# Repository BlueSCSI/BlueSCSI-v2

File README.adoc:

# BlueSCSI
:toc: macro

BlueSCSI is hardware that reproduces SCSI devices (hard disks, optical, etc) powered by the Raspberry Pi RP2040/RP2350.

This repository contains code for both BlueSCSI v2 and BlueSCSI Ultra/Ultra Wide.

image::docs/buynow.png[Buy Now,link=https://scsi.blue,width=150]
image::docs/discordbanner.png[Join our Discord,link=https://discord.gg/GKcvtgU7P9,width=150]

Join us in #bluescsi on https://discord.gg/GKcvtgU7P9[Discord] or open an issue on this repo.

## Hardware

Hardware schematics, designs, and production files can be found under the `hardware` folder.

Hardware version numbers are based on when the design was updated plus a sub-revision letter, such as "2022_11b" and "2022_12a".

You can find an errta of all the current and former versions in the wiki https://github.com/BlueSCSI/BlueSCSI-v2/wiki/Hardware

## Notes

### Making Gerbers for JLCPCB

https://support.jlcpcb.com/article/44-how-to-export-kicad-pcb-to-gerber-files

## Licenses

### Firmware

The BlueSCSI V2 firmware is a fork of ZuluSCSI, which also includes SCSI2SD V6 source code:

* https://github.com/ZuluSCSI/ZuluSCSI-firmware[ZuluSCSI]
* http://git.codesrc.com/index.cgi?p=SCSI2SD-V6.git;a=summary[SCSI2SD V6]
* https://github.com/erichelgeson/BlueSCSI[BlueSCSI V1]
* https://github.com/ztto/ArdSCSino-stm32[ArdSCSIno-stm32]

BlueSCSI(TM) - Eric Helgeson - All rights reserved.

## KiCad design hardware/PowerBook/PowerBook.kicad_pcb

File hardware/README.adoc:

BlueSCSI V2 Hardware
© 2022 - 2024 Tech by Androda, LLC

.All files in this hardware folder (and subfolders) are licensed CERN Open Hardware Licence Version 2 - Strongly Reciprocal:
* https://ohwr.org/cern_ohl_s_v2.txt[CERN Open Hardware Licence Version 2 - Strongly Reciprocal]

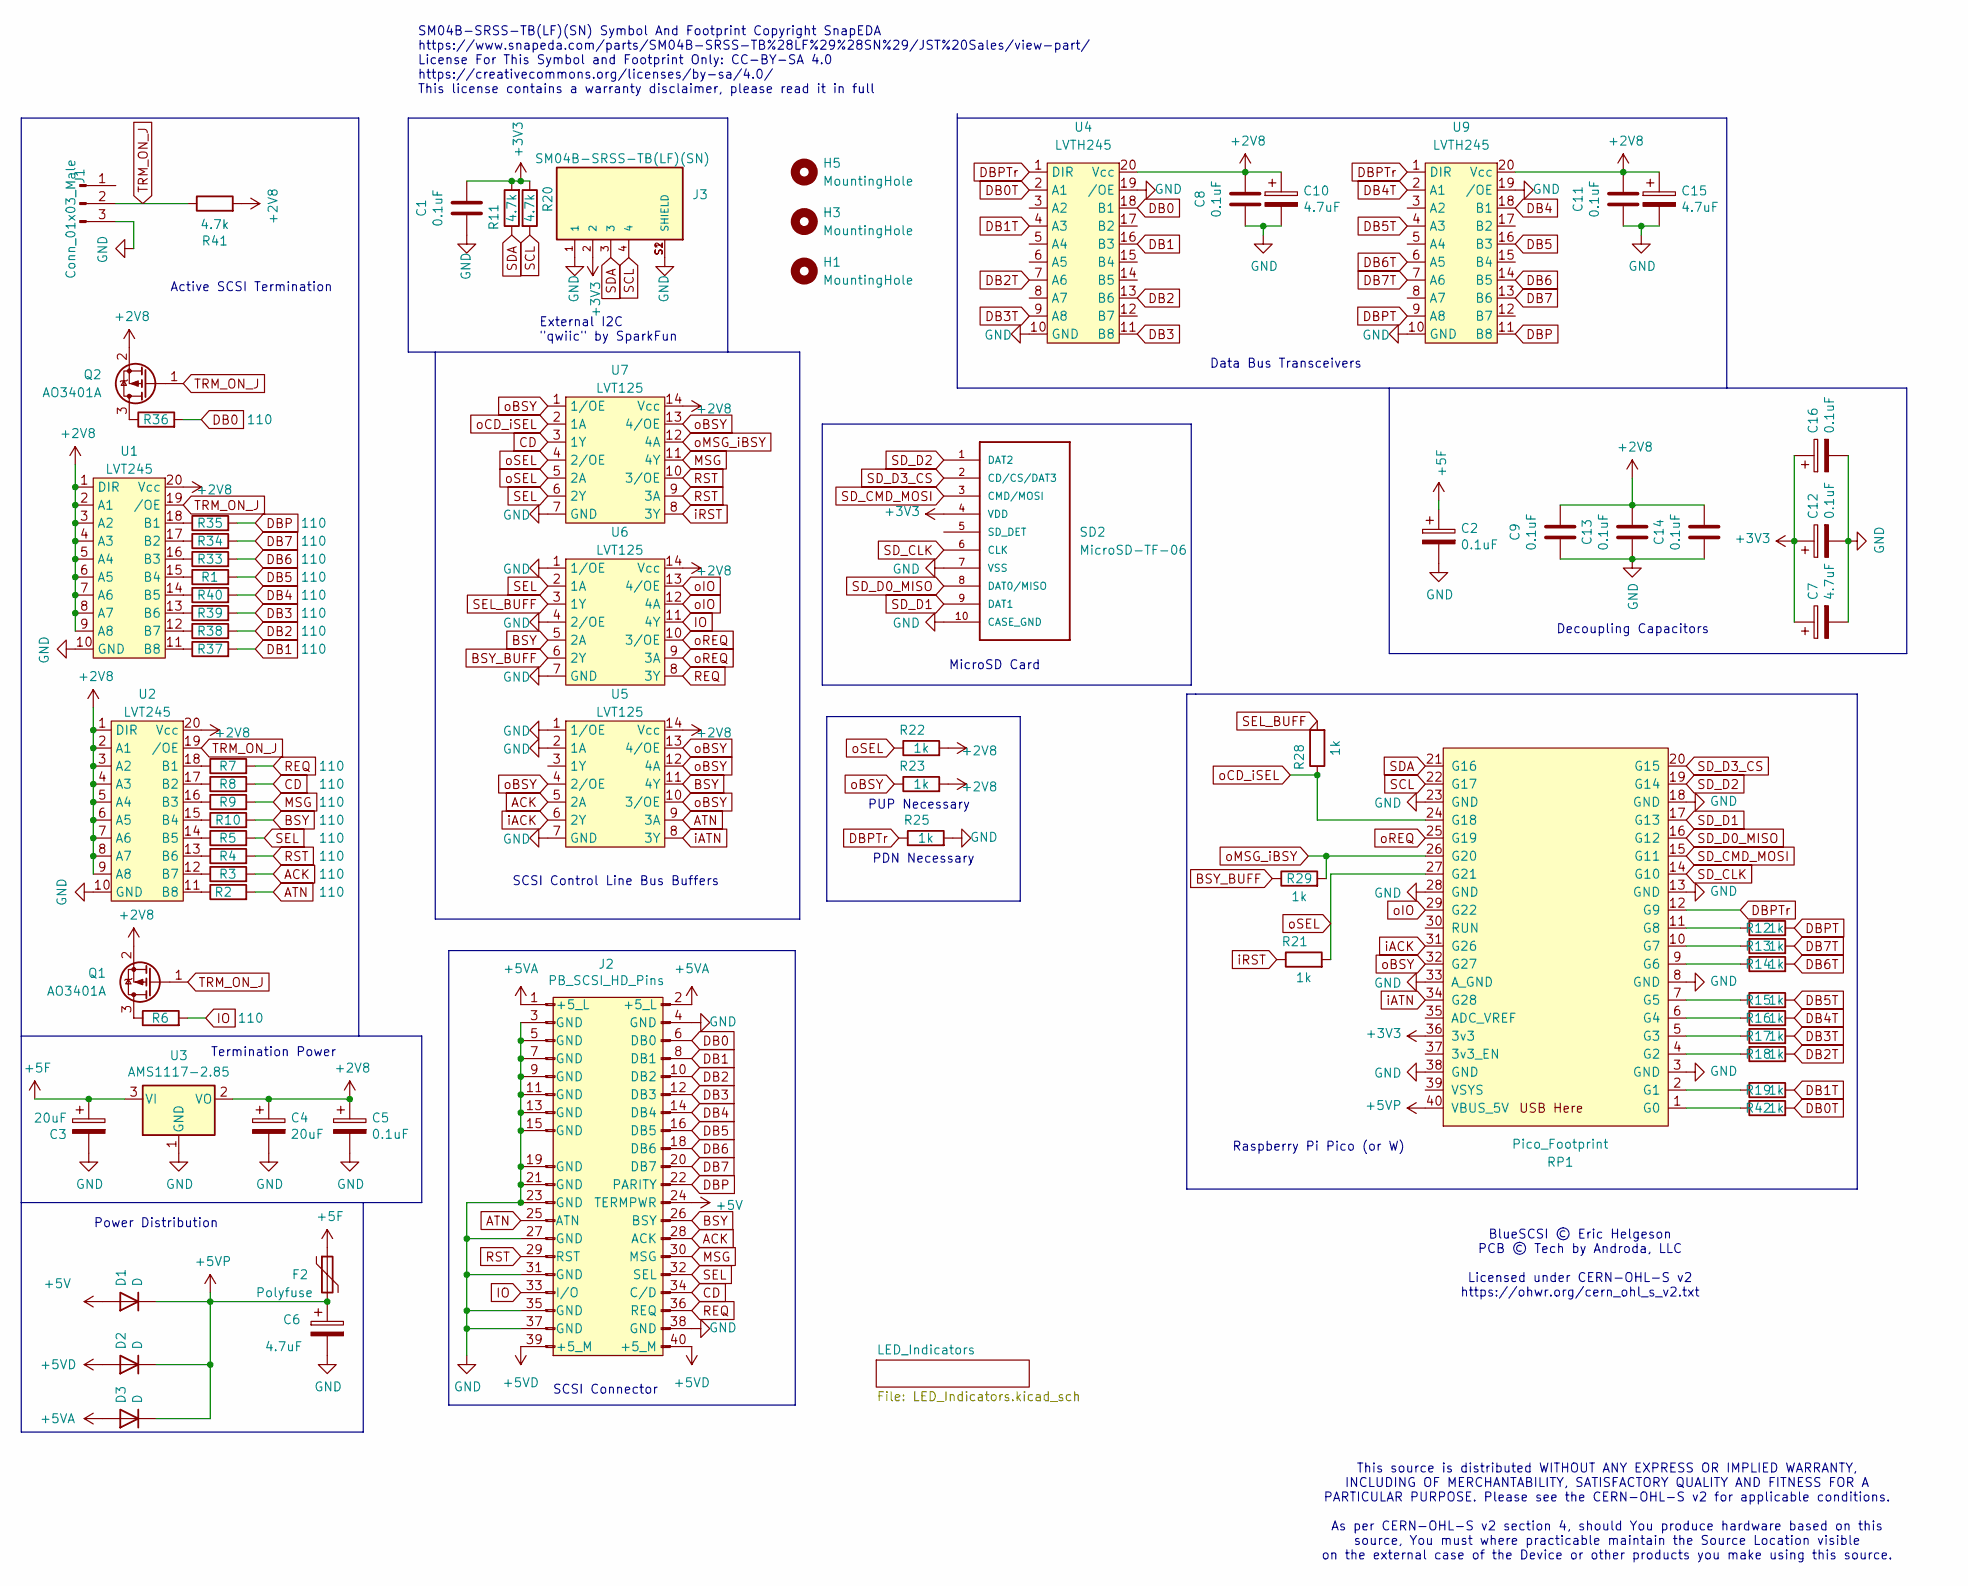
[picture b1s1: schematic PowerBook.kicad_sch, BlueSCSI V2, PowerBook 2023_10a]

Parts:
C1, C8, C9, C11, C13, C14: 0.1uF; C_0805_2012Metric_Pad1.18x1.45mm_HandSolder
C2, C5: 0.1uF; C_0805_2012Metric_Pad1.15x1.40mm_HandSolder
C3, C4: 20uF; C_1206_3216Metric_Pad1.42x1.75mm_HandSolder
C6: 4.7uF; C_0805_2012Metric_Pad1.15x1.40mm_HandSolder
C7: 4.7uF; C_0805_2012Metric
C10, C15: 4.7uF; C_0805_2012Metric_Pad1.18x1.45mm_HandSolder
C12, C16: 0.1uF; C_0805_2012Metric
D1, D2, D3: D; D_SMA
F2: Polyfuse; Fuse_0805_2012Metric_Pad1.15x1.40mm_HandSolder
H1, H3, H5: MountingHole; MountingHole_3.2mm_M3
J1: Conn_01x03_Male; PinHeader_1x03_P2.54mm_Vertical
J2: PB_SCSI_HD_Pins; PowerBook_SCSI_40Pin_UpsideDown
J3: SM04B-SRSS-TB(LF)(SN); JST_SM04B-SRSS-TB(LF)(SN)
Q1, Q2: AO3401A; SOT-23
R1, R2, R3, R4, R5, R6, R7, R8, R9, R10, R33, R34, R35, R36, R37, R38, R39, R40: 110; R_0603_1608Metric_Pad0.98x0.95mm_HandSolder
R11, R20: 4.7k; R_0603_1608Metric
R12, R13, R14, R15, R16, R17, R18, R19, R42: 1k; R_0402_1005Metric_Pad0.72x0.64mm_HandSolder
R21: 1k; R_0603_1608Metric
R22, R23, R25, R28, R29: 1k; R_0603_1608Metric_Pad0.98x0.95mm_HandSolder
R41: 4.7k; R_0603_1608Metric_Pad0.98x0.95mm_HandSolder
RP1: Pico_Footprint; Raspberry_Pi_PicoW_SMT_THT
SD2: MicroSD-TF-06; TF-06_MicroSD; MANUFACTURER_PART_NUMBER C693844
U1, U2: LVT245; TSSOP-20_4.4x6.5mm_P0.65mm
U3: AMS1117-2.85; SOT-223-3_TabPin2
U4, U9: LVTH245; TSSOP-20_4.4x6.5mm_P0.65mm
U5, U6, U7: LVT125; TSSOP-14_4.4x5mm_P0.65mm

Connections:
+2V8: C4.1, C5.1, C8.1, C9.2, C10.1, C11.1, C13.2, C14.2, C15.1, Q1.2 (S), Q2.2 (S), R22.2, R23.2, R41.2, U1.1 (DIR), U1.2 (A1), U1.3 (A2), U1.4 (A3), U1.5 (A4), U1.6 (A5), U1.7 (A6), U1.8 (A7), U1.9 (A8), U1.20 (Vcc), U2.1 (DIR), U2.2 (A1), U2.3 (A2), U2.4 (A3), U2.5 (A4), U2.6 (A5), U2.7 (A6), U2.8 (A7), U2.9 (A8), U2.20 (Vcc), U3.2 (VO), U4.20 (Vcc), U5.14 (Vcc), U6.14 (Vcc), U7.14 (Vcc), U9.20 (Vcc)
+3V3: C1.2, C7.1, C12.1, C16.1, J3.2, R11.2, R20.1, RP1.36 (3v3), SD2.4 (VDD); also elsewhere on the board
+5F: C2.1, C3.1, F2.1, U3.3 (VI); also elsewhere on the board
+5V: D1.2 (A), J2.24 (TERMPWR)
+5VA: D3.2 (A), J2.1 (+5_L), J2.2 (+5_L)
+5VD: D2.2 (A), J2.39 (+5_M), J2.40 (+5_M)
+5VP: C6.1, D1.1 (K), D2.1 (K), D3.1 (K), F2.2, RP1.40 (VBUS_5V)
ACK: J2.28 (ACK), R3.2, U5.5 (2A)
ATN: J2.25 (ATN), R2.2, U5.9 (3A)
BSY: J2.26 (BSY), R10.2, U5.11 (4Y), U6.5 (2A)
BSY_BUFF: R29.1, U6.6 (2Y)
CD: J2.34 (C/D), R8.2, U7.3 (1Y)
DB0: J2.6 (DB0), R36.2, U4.18 (B1)
DB0T: R42.2, U4.2 (A1)
DB1: J2.8 (DB1), R37.2, U4.16 (B3)
DB1T: R19.2, U4.4 (A3)
DB2: J2.10 (DB2), R38.2, U4.13 (B6)
DB2T: R18.2, U4.7 (A6)
DB3: J2.12 (DB3), R39.2, U4.11 (B8)
DB3T: R17.2, U4.9 (A8)
DB4: J2.14 (DB4), R40.2, U9.18 (B1)
DB4T: R16.2, U9.2 (A1)
DB5: J2.16 (DB5), R1.2, U9.16 (B3)
DB5T: R15.2, U9.4 (A3)
DB6: J2.18 (DB6), R33.2, U9.14 (B5)
DB6T: R14.2, U9.6 (A5)
DB7: J2.20 (DB7), R34.2, U9.13 (B6)
DB7T: R13.2, U9.7 (A6)
DBP: J2.22 (PARITY), R35.2, U9.11 (B8)
DBPT: R12.2, U9.9 (A8)
DBPTr: R25.1, RP1.12 (G9), U4.1 (DIR), U9.1 (DIR)
GND: C1.1, C2.2, C3.2, C4.2, C5.2, C6.2, C7.2, C8.2, C9.1, C10.2, C11.2, C12.2, C13.1, C14.1, C15.2, C16.2, J1.3, J2.3 (GND), J2.4 (GND), J2.5 (GND), J2.7 (GND), J2.9 (GND), J2.11 (GND), J2.13 (GND), J2.15 (GND), J2.19 (GND), J2.21 (GND), J2.23 (GND), J2.27 (GND), J2.31 (GND), J2.35 (GND), J2.37 (GND), J2.38 (GND), J3.1, J3.S1 (SHIELD), J3.S2 (SHIELD), R25.2, RP1.3 (GND), RP1.8 (GND), RP1.13 (GND), RP1.18 (GND), RP1.23 (GND), RP1.28 (GND), RP1.33 (A_GND), RP1.38 (GND), SD2.7 (VSS), SD2.10 (CASE_GND), U1.10 (GND), U2.10 (GND), U3.1 (GND), U4.10 (GND), U4.19 (/OE), U5.1 (1/OE), U5.2 (1A), U5.7 (GND), U6.1 (1/OE), U6.4 (2/OE), U6.7 (GND), U7.7 (GND), U9.10 (GND), U9.19 (/OE); also elsewhere on the board
IO: J2.33 (I/O), R6.2, U6.11 (4Y)
MSG: J2.30 (MSG), R9.2, U7.11 (4Y)
unnamed: Q1.3 (D), R6.1
unnamed: Q2.3 (D), R36.1
unnamed: R1.1, U1.15 (B4)
unnamed: R2.1, U2.11 (B8)
unnamed: R3.1, U2.12 (B7)
unnamed: R4.1, U2.13 (B6)
unnamed: R5.1, U2.14 (B5)
unnamed: R7.1, U2.18 (B1)
unnamed: R8.1, U2.17 (B2)
unnamed: R9.1, U2.16 (B3)
unnamed: R10.1, U2.15 (B4)
unnamed: R12.1, RP1.11 (G8)
unnamed: R13.1, RP1.10 (G7)
unnamed: R14.1, RP1.9 (G6)
unnamed: R15.1, RP1.7 (G5)
unnamed: R16.1, RP1.6 (G4)
unnamed: R17.1, RP1.5 (G3)
unnamed: R18.1, RP1.4 (G2)
unnamed: R19.1, RP1.2 (G1)
unnamed: R33.1, U1.16 (B3)
unnamed: R34.1, U1.17 (B2)
unnamed: R35.1, U1.18 (B1)
unnamed: R37.1, U1.11 (B8)
unnamed: R38.1, U1.12 (B7)
unnamed: R39.1, U1.13 (B6)
unnamed: R40.1, U1.14 (B5)
unnamed: R42.1, RP1.1 (G0)
REQ: J2.36 (REQ), R7.2, U6.8 (3Y)
RST: J2.29 (RST), R4.2, U7.9 (3A), U7.10 (3/OE)
SCL: J3.4, R20.2, RP1.22 (G17)
SDA: J3.3, R11.1, RP1.21 (G16)
SD_CLK: RP1.14 (G10), SD2.6 (CLK)
SD_CMD_MOSI: RP1.15 (G11), SD2.3 (CMD/MOSI)
SD_D0_MISO: RP1.16 (G12), SD2.8 (DAT0/MISO)
SD_D1: RP1.17 (G13), SD2.9 (DAT1)
SD_D2: RP1.19 (G14), SD2.1 (DAT2)
SD_D3_CS: RP1.20 (G15), SD2.2 (CD/CS/DAT3)
SEL: J2.32 (SEL), R5.2, U6.2 (1A), U7.6 (2Y)
SEL_BUFF: R28.2, U6.3 (1Y)
TRM_ON_J: J1.2, Q1.1 (G), Q2.1 (G), R41.1, U1.19 (/OE), U2.19 (/OE)
iACK: RP1.31 (G26), U5.6 (2Y)
iATN: RP1.34 (G28), U5.8 (3Y)
iRST: R21.1, U7.8 (3Y)
oBSY: R23.1, RP1.32 (G27), U5.4 (2/OE), U5.10 (3/OE), U5.12 (4A), U5.13 (4/OE), U7.1 (1/OE), U7.13 (4/OE); also elsewhere on the board
oCD_iSEL: R28.1, RP1.24 (G18), U7.2 (1A)
oIO: RP1.29 (G22), U6.12 (4A), U6.13 (4/OE)
oMSG_iBSY: R29.2, RP1.26 (G20), U7.12 (4A)
oREQ: RP1.25 (G19), U6.9 (3A), U6.10 (3/OE)
oSEL: R21.2, R22.1, RP1.27 (G21), U7.4 (2/OE), U7.5 (2A)

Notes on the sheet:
Power Distribution
BlueSCSI © Eric Helgeson PCB © Tech by Androda, LLC Licensed under CERN-OHL-S v2 https://ohwr.org/cern_ohl_s_v2.txt
SCSI Connector
Active SCSI Termination
PUP Necessary
MicroSD Card
Data Bus Transceivers
Decoupling Capacitors
SM04B-SRSS-TB(LF)(SN) Symbol And Footprint Copyright SnapEDA https://www.snapeda.com/parts/SM04B-SRSS-TB%28LF%29%28SN%29/JST%20Sales/view-part/ License For This Symbol and Footprint Only: CC-BY-SA 4.0 https://creativecommons.org/licenses/by-sa/4.0/ This license contains a warranty disclaimer, pleas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
This source is distributed WITHOUT ANY EXPRESS OR IMPLIED WARRANTY, INCLUDING OF MERCHANTABILITY, SATISFACTORY QUALITY AND FITNESS FOR A PARTICULAR PURPOSE. Please see the CERN-OHL-S v2 for applicable conditions. As per CERN-OHL-S v2 section 4, should You produce hardware based on this source, You 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
PDN Necessary
External I2C "qwiic" by SparkFun
Raspberry Pi Pico (or W)
Termination Power
SCSI Control Line Bus Buffers

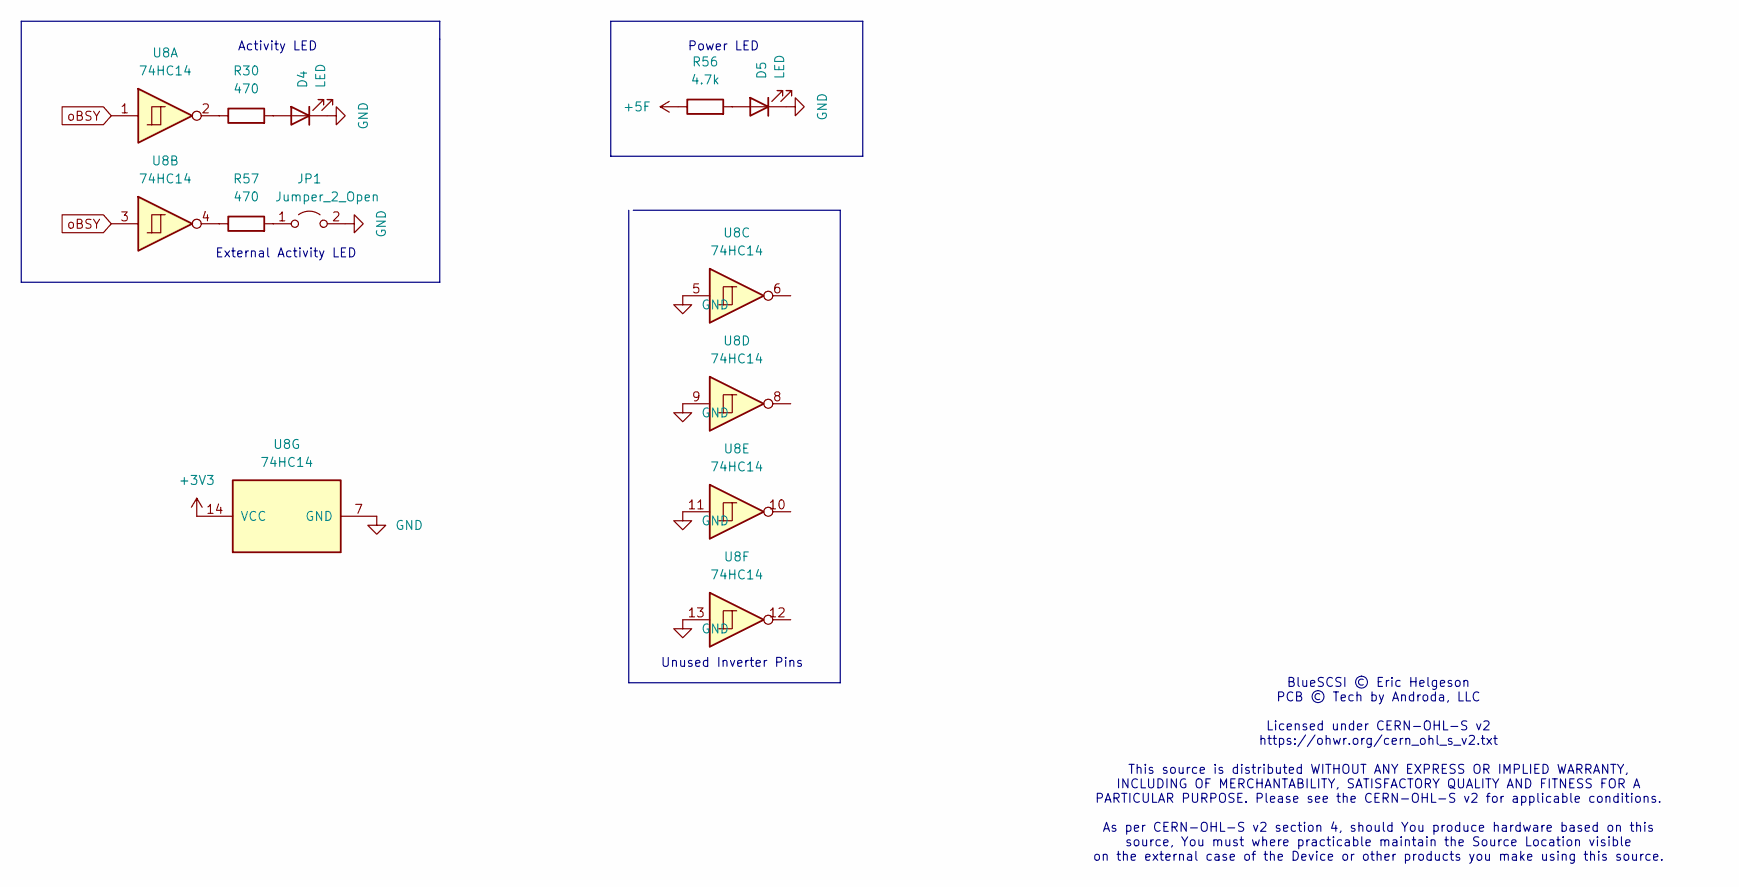
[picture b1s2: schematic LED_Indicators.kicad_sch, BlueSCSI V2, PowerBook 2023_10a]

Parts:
D4, D5: LED; LED_0603_1608Metric_Pad1.05x0.95mm_HandSolder
JP1: Jumper_2_Open; SolderJumper-2_P1.3mm_Open_Pad1.0x1.5mm
R30, R57: 470; R_0402_1005Metric_Pad0.72x0.64mm_HandSolder
R56: 4.7k; R_0603_1608Metric_Pad0.98x0.95mm_HandSolder
U8: 74HC14

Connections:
+3V3: U8.14 (VCC); also elsewhere on the board
+5F: R56.1; also elsewhere on the board
GND: D4.1 (K), D5.1 (K), JP1.2 (B), U8.5, U8.7 (GND), U8.9, U8.11, U8.13; also elsewhere on the board
unnamed: D4.2 (A), R30.2
unnamed: D5.2 (A), R56.2
unnamed: JP1.1 (A), R57.2
unnamed: R30.1, U8.2
unnamed: R57.1, U8.4
oBSY: U8.1, U8.3; also elsewhere on the board

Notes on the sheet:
BlueSCSI © Eric Helgeson PCB © Tech by Androda, LLC Licensed under CERN-OHL-S v2 https://ohwr.org/cern_ohl_s_v2.txt This source is distributed WITHOUT ANY EXPRESS OR IMPLIED WARRANTY, INCLUDING OF MERCHANTABILITY, SATISFACTORY QUALITY AND FITNESS FOR A PARTICULAR PURPOSE. Please see the CERN-OHL-S 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
Power LED
External Activity LED
Unused Inverter Pins
Activity LED

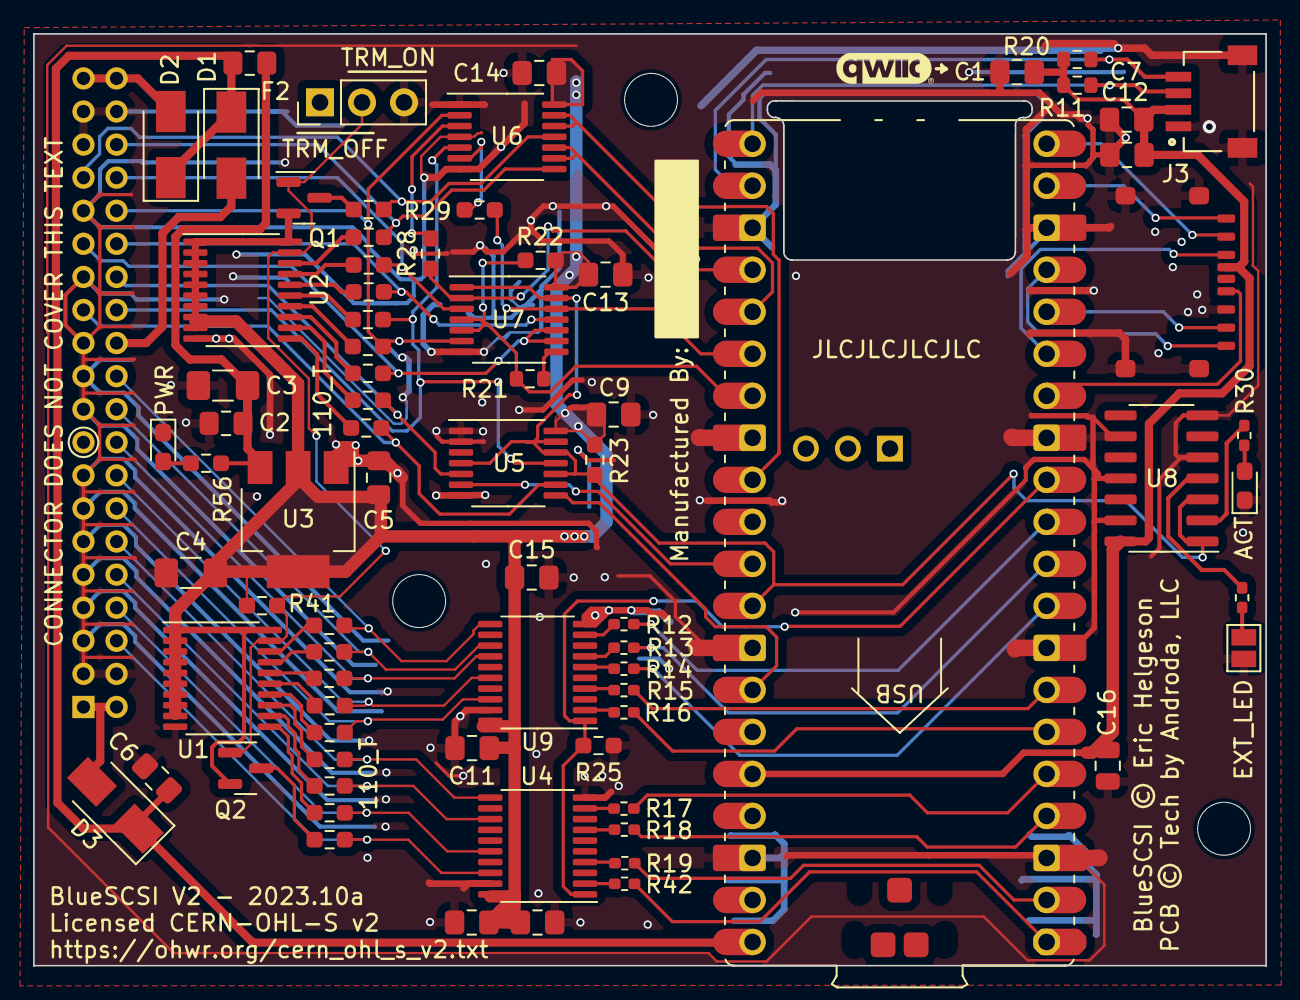
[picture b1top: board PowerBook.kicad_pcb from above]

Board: 2 copper layers, 74.5 x 56.3 mm, 81 parts (0 on the bottom side), 88 nets.

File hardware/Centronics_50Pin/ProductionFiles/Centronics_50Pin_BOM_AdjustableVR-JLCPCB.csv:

Comment,Designator,Footprint,LCSC Part #
LVT125,"U7,U5,U6",TSSOP-14_4.4x5mm_P0.65mm,C7042
20uF,C3,C_1206_3216Metric_Pad1.42x1.75mm_HandSolder,C5672
47uF,C4,C_1206_3216Metric_Pad1.42x1.75mm_HandSolder,C96123
AP1117-ADJ,U3,SOT-223-3_TabPin2,C233201
0.1uF,"C2,C5,C8,C14,C1,C9,C11,C13",C_0603_1608Metric,C14663
4.7uF,"C6,C12,C15,C10",C_0603_1608Metric,C19666
D,"D1,D4",D_SMA,C2480
1k,"R42,R16,R17,R13,R18,R15,R12,R19,R14",R_0402_1005Metric_Pad0.72x0.64mm_HandSolder,C11702
110,"R39,R4,R33,R36,R5,R35,R1,R38,R9,R40,R3,R7,R8,R2,R10,R34,R37,R6",R_0603_1608Metric_Pad0.98x0.95mm_HandSolder,C141676
LED,D2,LED_0603_1608Metric_Pad1.05x0.95mm_HandSolder,C72041
LED,D3,LED_0603_1608Metric_Pad1.05x0.95mm_HandSolder,C2290
4.7uF,C7,C_0805_2012Metric_Pad1.18x1.45mm_HandSolder,C1779
4.7k,"R56,R22,R23,R25",R_0603_1608Metric_Pad0.98x0.95mm_HandSolder,C23162
154,R20,R_0603_1608Metric,C22808
LVTH245,"U4,U9",TSSOP-20_4.4x6.5mm_P0.65mm,C2652121
74HC14,U8,SOIC-14_3.9x8.7mm_P1.27mm,C5605
470,R30,R_0402_1005Metric_Pad0.72x0.64mm_HandSolder,C25117
MicroSD-TF-06,SD2,TF-06_MicroSD,C693844
AO3401A,Q3,SOT-23,C15127
Polyfuse,"F2,F1",Fuse_0805_2012Metric_Pad1.15x1.40mm_HandSolder,C883111
10k,R11,R_0603_1608Metric,C25804
120,R21,R_0805_2012Metric,C17437
1k,"R29,R28",R_0603_1608Metric_Pad0.98x0.95mm_HandSolder,C21190
10uF,C16,C_0603_1608Metric,C19702

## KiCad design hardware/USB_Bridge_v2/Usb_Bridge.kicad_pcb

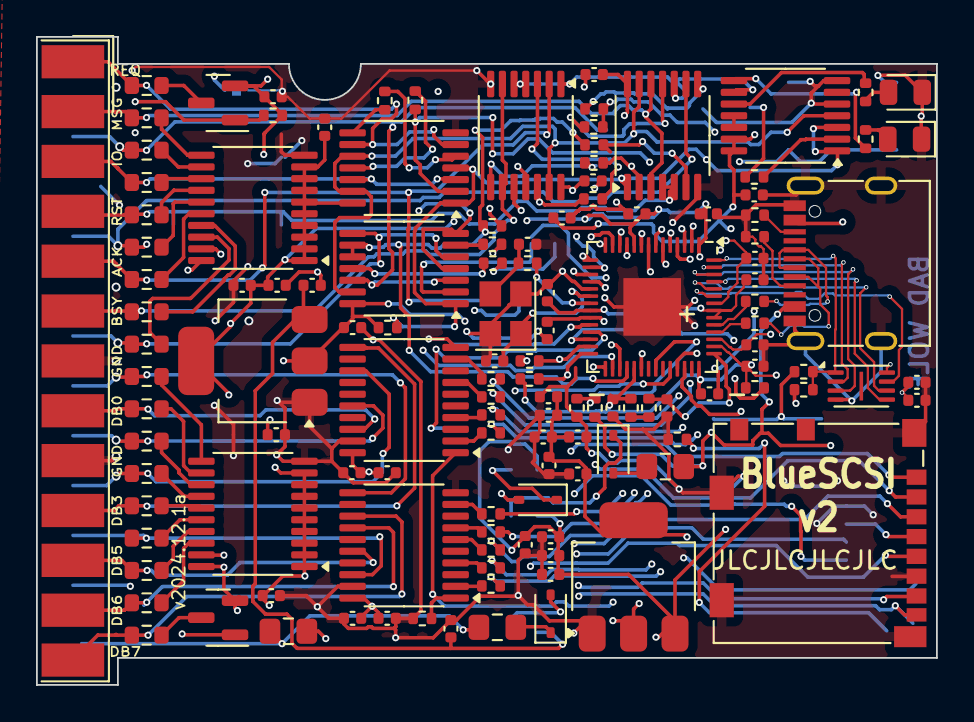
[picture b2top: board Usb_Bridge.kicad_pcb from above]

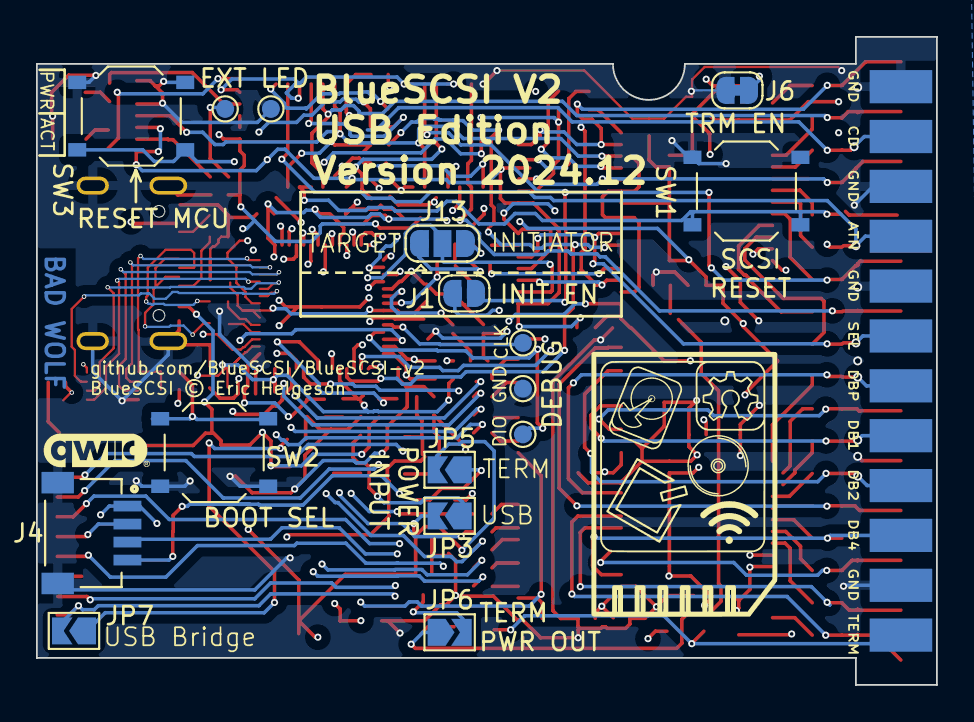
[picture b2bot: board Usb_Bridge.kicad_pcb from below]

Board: 4 copper layers, 50.0 x 36.0 mm, 143 parts (16 on the bottom side), 128 nets.

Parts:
C1, C2, C4, C5, C6, C10, C11, C12, C13, C14, C15, C16, C18, C21, C23, C28, C29, C30, C33, C34, C35, C36, C37, C39, C43: 0.1uF; C_0402_1005Metric
C3, C7, C8, C17, C22: 4.7uF; C_0402_1005Metric
C9, C19, C20, C24, C25, C26: 10uF; C_0402_1005Metric
C27, C31, C32, C38: 2.2u 6.3V; C_0402_1005Metric
C40, C42: 15p; C_0402_1005Metric
D1, D2: LED; LED_0805_2012Metric
D3, D8, D9: Schottky Diode; D_SOD-323
F1, F3, F5: Polyfuse; Fuse_0805_2012Metric_Pad1.15x1.40mm_HandSolder
J1: ACK_En; SolderJumper-2_P1.3mm_Open_RoundedPad1.0x1.5mm
J3: SCSI Connector; DSUB-25_Male_EdgeMount_P2.77mm
J4: SM04B-SRSS-TB(LF)(SN); JST_SM04B-SRSS-TB(LF)(SN)
J6: Conn_01x03_Male; SolderJumper-2_P1.3mm_Bridged_RoundedPad1.0x1.5mm
J12: USB_C_Receptacle_USB2.0; USB_C_Receptacle_G-Switch_GT-USB-7010ASV
J13: Conn_01x03_Male; SolderJumper-3_P1.3mm_Open_RoundedPad1.0x1.5mm
JP3: USB Pwr En; SolderJumper-2_P1.3mm_Open_TrianglePad1.0x1.5mm
JP5: Term Input Pwr En; SolderJumper-2_P1.3mm_Open_TrianglePad1.0x1.5mm
JP6: Term Output En; SolderJumper-2_P1.3mm_Open_TrianglePad1.0x1.5mm
JP7: USB Bridge En; SolderJumper-2_P1.3mm_Open_TrianglePad1.0x1.5mm
Q1, Q2: AO3401A; SOT-23
R1, R2, R4, R9, R58, R79, R80, R81, R82, R83, R84, R85, R86, R87, R88, R89, R90, R91, R92, R93, R94, R95, R96: 1k; R_0402_1005Metric
R5, R7, R22, R23, R25, R46: 4.7k; R_0402_1005Metric
R24: 470; R_0402_1005Metric
R27: 330; R_0402_1005Metric
R28, R29, R30, R31, R32, R33, R34, R35, R36, R37, R38, R39, R40, R41, R42, R43, R44, R45: 110; R_0603_1608Metric
R47, R48: 5.1k; R_0402_1005Metric
R49: 5.6k; R_0402_1005Metric
R50: 200R; R_0402_1005Metric
R51: 10k; R_0402_1005Metric
R52: 1R; R_0402_1005Metric
R55: NO-FIT; R_0402_1005Metric
R56, R57: 27R; R_0402_1005Metric
SD1: Micro SD Card; microSD_HC_Molex_104031-0811
SW1: SCSI Reset; SW_Push_1P1T_XKB_TS-1187A
SW2: USB Boot; SW_Push_1P1T_XKB_TS-1187A
SW3: RP2040 Reset; SW_Push_1P1T_XKB_TS-1187A
TP1, TP2, TP3, TP4, TP5: TestPoint_Small; TestPoint_Pad_D1.0mm
U1, U2, U3, U4: LVT125; TSSOP-14_4.4x5mm_P0.65mm
U5: 74HC14; TSSOP-14_4.4x5mm_P0.65mm
U6, U7, U8, U9: LVT245; TSSOP-20_4.4x6.5mm_P0.65mm
U10: AMS1117-2.85; SOT-223-3_TabPin2
U11: AMS1117-3.3; SOT-223-3_TabPin2
U12: W25Q16JVUXIQ; Winbond_USON-8-1EP_3x2mm_P0.5mm_EP0.2x1.6mm
U13: RP2040; QFN-56-1EP_7x7mm_P0.4mm_EP3.2x3.2mm
Y1: 12MHz; Crystal_SMD_3225-4Pin_3.2x2.5mm

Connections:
!oBSY: U1.10 (3/OE), U1.13 (4/OE), U2.13 (4/OE), U3.13 (4/OE), U4.13 (4/OE), U5.4
+1V1: C32.1, C36.1, C37.1, U13.23 (DVDD), U13.45 (VREG_VOUT), U13.50 (DVDD)
+2V8: C2.1, C3.1, C4.1, C5.1, C6.1, C7.1, C9.1, C10.1, C13.2, C14.2, C15.2, C16.2, C24.1, Q1.2 (S), Q2.2 (S), R5.2, R7.2, R46.2, U1.14 (Vcc), U2.14 (Vcc), U3.14 (Vcc), U4.14 (Vcc), U6.20 (Vcc), U7.1 (DIR), U7.2 (A1), U7.3 (A2), U7.4 (A3), U7.5 (A4), U7.6 (A5), U7.7 (A6), U7.8 (A7), U7.9 (A8), U7.20 (Vcc), U8.1 (DIR), U8.2 (A1), U8.3 (A2), U8.4 (A3), U8.5 (A4), U8.6 (A5), U8.7 (A6), U8.8 (A7), U8.9 (A8), U8.20 (Vcc), U9.20 (Vcc), U10.2 (VO)
+3V3: C1.2, C17.1, C18.1, C25.1, C26.1, C28.1, C29.1, C30.1, C31.1, C33.1, C34.1, C35.1, C38.1, C39.1, C43.1, J4.2, R1.1, R22.2, R23.1, R50.1, R55.1, SD1.4 (VDD), U11.2 (VO), U12.8 (VCC), U13.1 (IOVDD), U13.10 (IOVDD), U13.22 (IOVDD), U13.33 (IOVDD), U13.42 (IOVDD), U13.44 (VREG_VIN), U13.48 (USB_VDD), U13.49 (IOVDD)
+5V: C8.1, C11.1, C12.1, C19.1, C20.1, C21.1, C22.1, C23.2, JP3.2 (B), JP5.2 (B), JP6.1 (A), U5.13, U5.14 (VCC), U10.3 (VI), U11.3 (VI)
/Pico/ADC_AVDD: C27.1, R52.2, U13.43 (ADC_AVDD)
/Pico/ADC_VREF: R50.2, R52.1
/Pico/GPIO00: R96.1, U13.2 (GPIO0)
/Pico/GPIO01: R95.1, U13.3 (GPIO1)
/Pico/GPIO02: R93.1, U13.4 (GPIO2)
/Pico/GPIO03: R92.1, U13.5 (GPIO3)
/Pico/GPIO04: R91.1, U13.6 (GPIO4)
/Pico/GPIO05: R89.1, U13.7 (GPIO5)
/Pico/GPIO06: R88.1, U13.8 (GPIO6)
/Pico/GPIO07: R87.1, U13.9 (GPIO7)
/Pico/GPIO08: R85.1, U13.11 (GPIO8)
/Pico/GPIO24: R49.2, R51.1, U13.36 (GPIO24)
/Pico/GPIO28: R90.1, R94.1, U13.40 (GPIO28/ADC2)
/Pico/QSPI_SCLK: U12.6 (CLK), U13.52 (QSPI_SCLK)
/Pico/QSPI_SD0: U12.5 (DI(IO0)), U13.53 (QSPI_SD0)
/Pico/QSPI_SD1: U12.2 (DO(IO1)), U13.55 (QSPI_SD1)
/Pico/QSPI_SD2: U12.3 (IO2), U13.54 (QSPI_SD2)
/Pico/QSPI_SD3: U12.7 (IO3), U13.51 (QSPI_SD3)
/Pico/QSPI_SS: R55.2, R58.1, U12.1 (~CS), U13.56 (QSPI_SS_N)
/Pico/RUN: R1.2, SW3.2, U13.26 (RUN)
/Pico/SWCLK: TP1.1, U13.24 (SWCLK)
/Pico/SWDIO: TP3.1, U13.25 (SWDIO)
/Pico/USB_D+: J12.A6 (D+), J12.B6 (D+), R56.1
/Pico/USB_D-: J12.A7 (D-), J12.B7 (D-), R57.1
/Pico/XIN: C42.1, U13.20 (XIN), Y1.1
/Pico/XOUT: R2.1, U13.21 (XOUT)
ACK: J1.1, J3.5, R32.2, U4.2 (1A)
ACKDr: J1.2, U4.11 (4Y)
ATN: J3.17, R34.2, U3.9 (3A)
BSY: J3.6, R30.2, U4.6 (2Y), U4.9 (3A)
CD: J3.15, R40.2, U2.3 (1Y), U2.12 (4A)
DB0: J3.8, R41.2, U6.18 (B1)
DB0T: R96.2, U6.2 (A1)
DB1: J3.21, R39.2, U6.16 (B3)
DB1T: R95.2, U6.4 (A3)
DB2: J3.22, R37.2, U6.13 (B6)
DB2T: R93.2, U6.7 (A6)
DB3: J3.10, R35.2, U6.11 (B8)
DB3T: R92.2, U6.9 (A8)
DB4: J3.23, R33.2, U9.18 (B1)
DB4T: R91.2, U9.2 (A1)
DB5: J3.11, R31.2, U9.16 (B3)
DB5T: R89.2, U9.4 (A3)
DB6: J3.12, R29.2, U9.14 (B5)
DB6T: R88.2, U9.6 (A5)
DB7: J3.13, R44.2, U9.13 (B6)
DB7T: R87.2, U9.7 (A6)
DBP: J3.20, R43.2, U9.11 (B8)
DBPT: R85.2, U9.9 (A8)
DBPTr: R9.1, U6.1 (DIR), U9.1 (DIR), U13.12 (GPIO9)
EXT_TERM_PWR: F1.1, F5.2, J3.25
GND: C1.1, C2.2, C3.2, C4.2, C5.2, C6.2, C7.2, C8.2, C9.2, C10.2, C11.2, C12.2, C13.1, C14.1, C15.1, C16.1, C17.2, C18.2, C19.2, C20.2, C21.2, C22.2, C23.1, C24.2, C25.2, C26.2, C27.2, C28.2, C29.2, C30.2, C31.2, C32.2, C33.2, C34.2, C35.2, C36.2, C37.2, C38.2, C39.2, C40.2, C42.2, C43.2, D1.1 (K), D2.1 (K), J3.7, J3.9, J3.14, J3.16, J3.18, J3.24, J4.1, J4.S1 (SHIELD), J4.S2 (SHIELD), J6.2, J12.A1 (GND), J12.A12 (GND), J12.B1 (GND), J12.B12 (GND), J12.S1 (SHIELD), R4.2, R9.2, R47.1, R48.2, R51.2, SD1.6 (VSS), SD1.11 (SHIELD), SW1.1, SW2.1, SW3.1, TP2.1, TP4.1, U1.7 (GND), U2.4 (2/OE), U2.7 (GND), U3.7 (GND), U4.7 (GND), U4.10 (3/OE), U5.5, U5.7 (GND), U6.10 (GND), U6.19 (/OE), U7.10 (GND), U8.10 (GND), U9.10 (GND), U9.19 (/OE), U10.1 (GND), U11.1 (GND), U12.4 (GND), U13.19 (TESTEN), U13.57 (GND), Y1.2, Y1.4
IO: J3.3, R38.2, U1.3 (1Y), U1.12 (4A)
MSG: J3.2, R42.2, U3.3 (1Y), U3.12 (4A)
unnamed: C40.1, R2.2, Y1.3
unnamed: D1.2 (A), R24.2
unnamed: D2.2 (A), R25.2
unnamed: D3.2 (A), JP6.2 (B)
unnamed: D3.1 (K), F1.2
unnamed: D8.2 (A), F3.1
unnamed: D8.1 (K), JP3.1 (A)
unnamed: D9.2 (A), F5.1
unnamed: D9.1 (K), JP5.1 (A)
unnamed: J12.A5 (CC1), R48.1
unnamed: J12.B5 (CC2), R47.2
unnamed: J13.1, R80.2
unnamed: J13.3, R79.2
unnamed: JP7.1 (A), R4.1
unnamed: Q1.3 (D), R44.1
unnamed: Q2.3 (D), R45.1
unnamed: R24.1, U5.8
unnamed: R25.1, U5.10
unnamed: R27.1, U5.2
unnamed: R27.2, TP5.1
unnamed: R58.2, SW2.2
unnamed: U5.11, U5.12
unnamed: R28.1, U7.18 (B1)
unnamed: R30.1, U7.17 (B2)
unnamed: R32.1, U7.16 (B3)
unnamed: R34.1, U7.15 (B4)
unnamed: R36.1, U7.14 (B5)
unnamed: R38.1, U7.13 (B6)
unnamed: R40.1, U7.12 (B7)
unnamed: R42.1, U7.11 (B8)
unnamed: R29.1, U8.18 (B1)
unnamed: R31.1, U8.17 (B2)
unnamed: R33.1, U8.16 (B3)
unnamed: R35.1, U8.15 (B4)
unnamed: R37.1, U8.14 (B5)
unnamed: R39.1, U8.13 (B6)
unnamed: R41.1, U8.12 (B7)
unnamed: R43.1, U8.11 (B8)
unnamed: R57.2, U13.46 (USB_DM)
unnamed: R56.2, U13.47 (USB_DP)
REQ: J3.1, R45.2, U1.6 (2Y), U1.9 (3A)
RST: J3.4, R36.2, SW1.2, U3.4 (2/OE), U3.5 (2A)
SCL: J4.4, R23.2, U13.28 (GPIO17)
SDA: J4.3, R22.1, U13.27 (GPIO16)
SD_CLK: SD1.5 (CLK), U13.13 (GPIO10)
SD_CMD_MOSI: SD1.3 (CMD), U13.14 (GPIO11)
SD_D0_MISO: SD1.7 (DAT0), U13.15 (GPIO12)
SD_D1: JP7.2 (B), SD1.8 (DAT1), U13.16 (GPIO13)
SD_D2: SD1.1 (DAT2), U13.17 (GPIO14)
SD_D3_CS: SD1.2 (DAT3/CD), U13.18 (GPIO15)
SEL: J3.19, R28.2, U2.5 (2A), U2.8 (3Y)
TRM_ON_J: J6.1, Q1.1 (G), Q2.1 (G), R46.1, U7.19 (/OE), U8.19 (/OE)
VBUS: F3.2, J12.A4 (VBUS), J12.A9 (VBUS), J12.B4 (VBUS), J12.B9 (VBUS), R49.1
iACK: R86.2, U4.3 (1Y)
iATN: R90.2, U3.8 (3Y)
iBSY: R82.1, U4.8 (3Y)
iCD: R80.1, U2.11 (4Y)
iIO: R84.1, U1.11 (4Y)
iMSG: R94.2, U3.11 (4Y)
iREQ: R81.2, U1.8 (3Y)
iRST: R83.1, U3.6 (2Y)
iSEL: R79.1, U2.6 (2Y)
oACK: R86.1, U4.12 (4A), U13.38 (GPIO26/ADC0)
oBSY: R7.1, U1.1 (1/OE), U1.4 (2/OE), U2.1 (1/OE), U3.1 (1/OE), U3.10 (3/OE), U4.1 (1/OE), U4.4 (2/OE), U4.5 (2A), U5.1, U5.3, U5.9, U13.39 (GPIO27/ADC1)
oCD_iSEL: J13.2, U2.2 (1A), U13.29 (GPIO18)
oIO: R84.2, U1.2 (1A), U13.34 (GPIO22)
oMSG_iBSY: R82.2, U3.2 (1A), U13.31 (GPIO20)
oREQ: R81.1, U1.5 (2A), U13.30 (GPIO19)
oSEL: R5.1, R83.2, U2.9 (3A), U2.10 (3/OE), U13.32 (GPIO21)

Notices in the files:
cc-nc-hardware/Centronics_50Pin/LED_Indicators.kicad_sch:
© 2023 - 2024 Tech by Androda, LLC
cc-nc-hardware/DB25_External/LED_Indicators.kicad_sch:
© 2023 Tech by Androda, LLC
hardware/PowerBook/PowerBook.kicad_pcb:
Licensed CERN-OHL-S v2
hardware/USB_Bridge_v2/Usb_Bridge.kicad_pcb:
PCB © akuker & Tech by Androda, LLC
hw/desktop-50-pin/bluepill_scsi.kicad_pcb:
BlueSCSI(TM) © Eric Helgeson https://github.com/erichelgeson/bluescsi
BlueSCSI(TM) © Eric Helgeson 2021
parts and their libraries:
Public Domain As Per:
License: CC-BY-SA 4.0
